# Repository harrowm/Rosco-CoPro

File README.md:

# Rosco-CoPro
A 68882 floating point coprocessor board for the rosco_m68k SBC

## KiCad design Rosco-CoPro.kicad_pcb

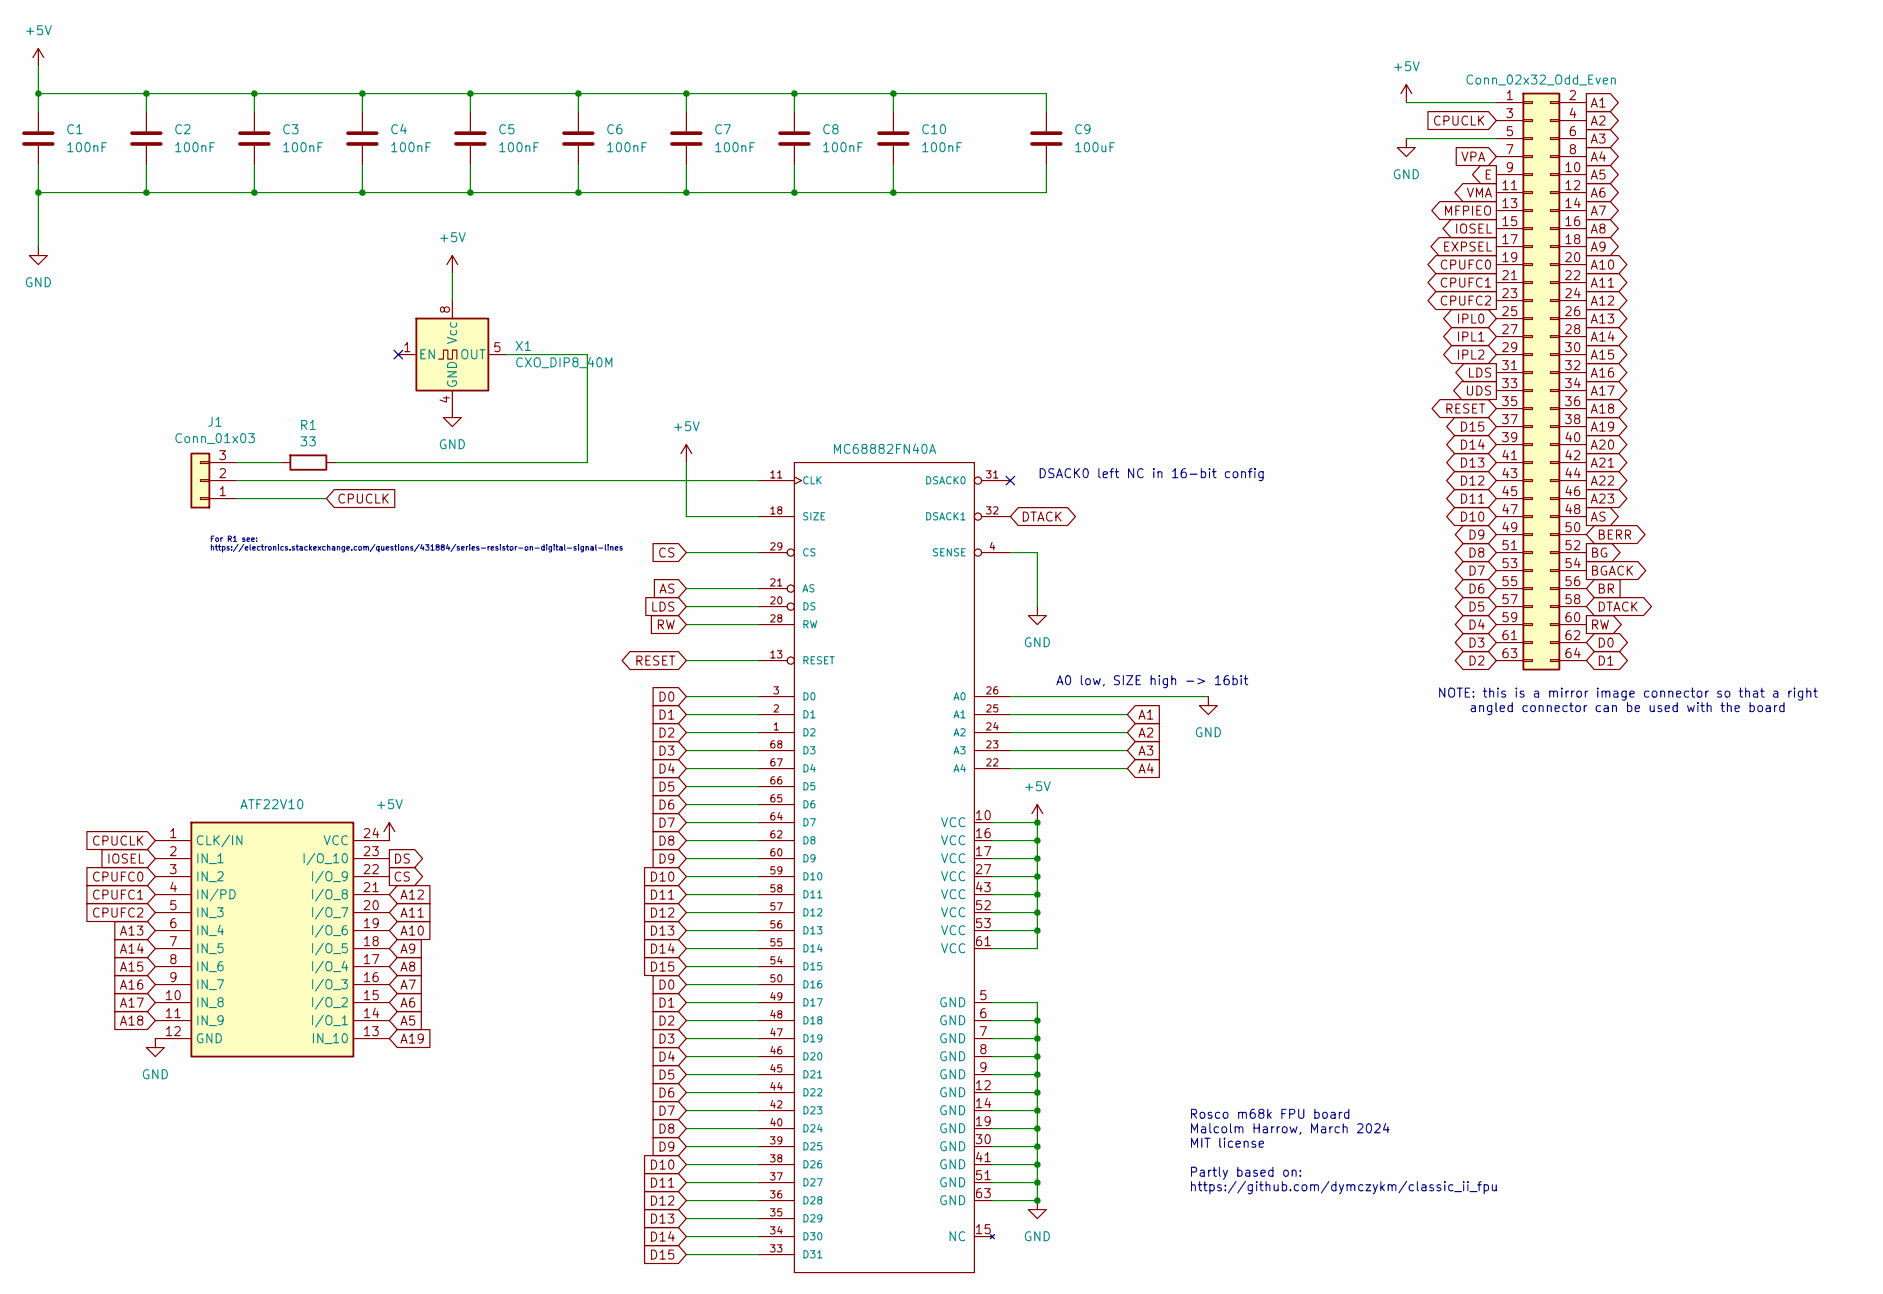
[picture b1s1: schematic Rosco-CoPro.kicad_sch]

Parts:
BUS1: Conn_02x32_Odd_Even; PinHeader_2x32_P2.54mm_Vertical
C1, C2, C3, C4, C5, C6, C7, C8, C10: 100nF; C_0805_2012Metric_Pad1.18x1.45mm_HandSolder; LCSC C49678
C9: 100uF; CP_Radial_D5.0mm_P2.50mm
IC1: MC68882FN40A; PLCC-68_THT-Socket
IC2: ATF22V10; DIP-24_W7.62mm_LongPads; Mouser Part Number 556-AF22V10C15PU
J1: Conn_01x03; PinHeader_1x03_P2.54mm_Vertical
R1: 33; R_0805_2012Metric_Pad1.20x1.40mm_HandSolder; LCSC C17634
X1: CXO_DIP8_40M; Oscillator_DIP-8_LargePads

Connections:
+5V: BUS1.1, C1.1, C2.1, C3.1, C4.1, C5.1, C6.1, C7.1, C8.1, C9.1, C10.1, IC1.10 (VCC), IC1.16 (VCC), IC1.17 (VCC), IC1.18 (SIZE), IC1.27 (VCC), IC1.43 (VCC), IC1.52 (VCC), IC1.53 (VCC), IC1.61 (VCC), IC2.24 (VCC), X1.8 (Vcc)
A1: BUS1.2, IC1.25 (A1)
A2: BUS1.4, IC1.24 (A2)
A3: BUS1.6, IC1.23 (A3)
A4: BUS1.8, IC1.22 (A4)
A5: BUS1.10, IC2.14 (I/O_1)
A6: BUS1.12, IC2.15 (I/O_2)
A7: BUS1.14, IC2.16 (I/O_3)
A8: BUS1.16, IC2.17 (I/O_4)
A9: BUS1.18, IC2.18 (I/O_5)
A10: BUS1.20, IC2.19 (I/O_6)
A11: BUS1.22, IC2.20 (I/O_7)
A12: BUS1.24, IC2.21 (I/O_8)
A13: BUS1.26, IC2.6 (IN_4)
A14: BUS1.28, IC2.7 (IN_5)
A15: BUS1.30, IC2.8 (IN_6)
A16: BUS1.32, IC2.9 (IN_7)
A17: BUS1.34, IC2.10 (IN_8)
A18: BUS1.36, IC2.11 (IN_9)
A19: BUS1.38, IC2.13 (IN_10)
A20: BUS1.40
A21: BUS1.42
A22: BUS1.44
A23: BUS1.46
AS: BUS1.48, IC1.21 (AS)
BERR: BUS1.50
BG: BUS1.52
BGACK: BUS1.54
BR: BUS1.56
CPUCLK: BUS1.3, IC2.1 (CLK/IN), J1.1
CPUFC0: BUS1.19, IC2.3 (IN_2)
CPUFC1: BUS1.21, IC2.4 (IN/PD)
CPUFC2: BUS1.23, IC2.5 (IN_3)
CS: IC1.29 (CS), IC2.22 (I/O_9)
D0: BUS1.62, IC1.3 (D0), IC1.50 (D16)
D1: BUS1.64, IC1.2 (D1), IC1.49 (D17)
D2: BUS1.63, IC1.1 (D2), IC1.48 (D18)
D3: BUS1.61, IC1.47 (D19), IC1.68 (D3)
D4: BUS1.59, IC1.46 (D20), IC1.67 (D4)
D5: BUS1.57, IC1.45 (D21), IC1.66 (D5)
D6: BUS1.55, IC1.44 (D22), IC1.65 (D6)
D7: BUS1.53, IC1.42 (D23), IC1.64 (D7)
D8: BUS1.51, IC1.40 (D24), IC1.62 (D8)
D9: BUS1.49, IC1.39 (D25), IC1.60 (D9)
D10: BUS1.47, IC1.38 (D26), IC1.59 (D10)
D11: BUS1.45, IC1.37 (D27), IC1.58 (D11)
D12: BUS1.43, IC1.36 (D28), IC1.57 (D12)
D13: BUS1.41, IC1.35 (D29), IC1.56 (D13)
D14: BUS1.39, IC1.34 (D30), IC1.55 (D14)
D15: BUS1.37, IC1.33 (D31), IC1.54 (D15)
DS: IC2.23 (I/O_10)
DTACK: BUS1.58, IC1.32 (DSACK1)
E: BUS1.9
EXPSEL: BUS1.17
GND: BUS1.5, C1.2, C2.2, C3.2, C4.2, C5.2, C6.2, C7.2, C8.2, C9.2, C10.2, IC1.4 (SENSE), IC1.5 (GND), IC1.6 (GND), IC1.7 (GND), IC1.8 (GND), IC1.9 (GND), IC1.12 (GND), IC1.14 (GND), IC1.19 (GND), IC1.26 (A0), IC1.30 (GND), IC1.41 (GND), IC1.51 (GND), IC1.63 (GND), IC2.12 (GND), X1.4 (GND)
IOSEL: BUS1.15, IC2.2 (IN_1)
IPL0: BUS1.25
IPL1: BUS1.27
IPL2: BUS1.29
LDS: BUS1.31, IC1.20 (DS)
MFPIEO: BUS1.13
unnamed: IC1.11 (CLK), J1.2
unnamed: J1.3, R1.2
unnamed: R1.1, X1.5 (OUT)
RESET: BUS1.35, IC1.13 (RESET)
RW: BUS1.60, IC1.28 (RW)
UDS: BUS1.33
VMA: BUS1.11
VPA: BUS1.7

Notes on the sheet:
Rosco m68k FPU board Malcolm Harrow, March 2024 MIT license Partly based on: https://github.com/dymczykm/classic_ii_fpu
A0 low, SIZE high -> 16bit
For R1 see: https://electronics.stackexchange.com/questions/431884/series-resistor-on-digital-signal-lines
DSACK0 left NC in 16-bit config
NOTE: this is a mirror image connector so that a right angled connector can be used with the board

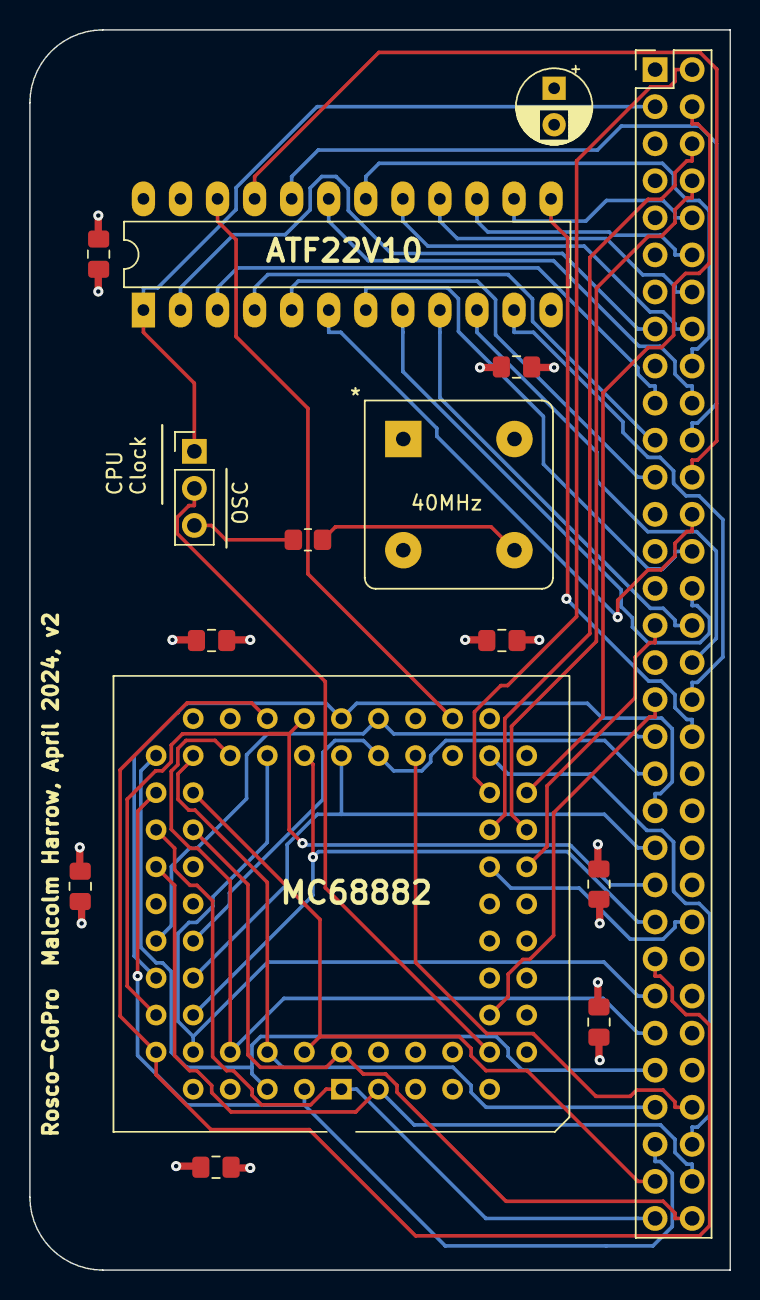
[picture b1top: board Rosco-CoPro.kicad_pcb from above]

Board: 4 copper layers, 48.0 x 85.0 mm, 15 parts (0 on the bottom side), 51 nets.

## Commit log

2024-03-01 Tidy up .gitignore
2024-03-03 Added manufacturing files
2024-03-10 Added in sample code
2024-03-10 Added very trivial example ..
2024-03-11 Added in example0 program - a very simple example
2024-03-16 Added more examples
2024-03-17 Basic working c and asm code examples
2024-03-17 Tidy up examples
2024-03-17 Get math header files working
2024-03-19 Added in whetstone test
2024-04-09 v2 board plus improvements to test suite
2024-04-10 Automated test compilation
2024-04-23 Further testing
2024-05-26 Tidy up pld
